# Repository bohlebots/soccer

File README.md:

# Bohlebots
<h2>collection of all published and open source software and hardware from the Bohlebots.</h2>
We are a team of students at the Gymnasium Haan in Germany. We call ourselves Bohlebots
due to the support of the Bohle company at our home town Haan.

We decided to put all our robotic stuff opensource. This includes arduino files and libraries,
eagle pcb files () and eagle libraries (lbr) for all our baords.
This page is under construction and it suffers from the inactivity of the author.
BUT:

We are also taking part at the development of the https://github.com/CoRoSoN-Kit/CoRoSoN-Kit.
The aktual bohlbots CoRoSoN Kit is lokated under https://github.com/ItzJannis/CoRoSoN-Package_Draft

Here is a photo of the prototypes of a mainboard and an IR-seeker-ring:

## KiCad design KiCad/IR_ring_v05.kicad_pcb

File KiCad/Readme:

These are the current KiCad project files of the season 2024.
These boards are used by the bohlebots 1vs1 teams and can be used as CoRoSoN Kit boards as well

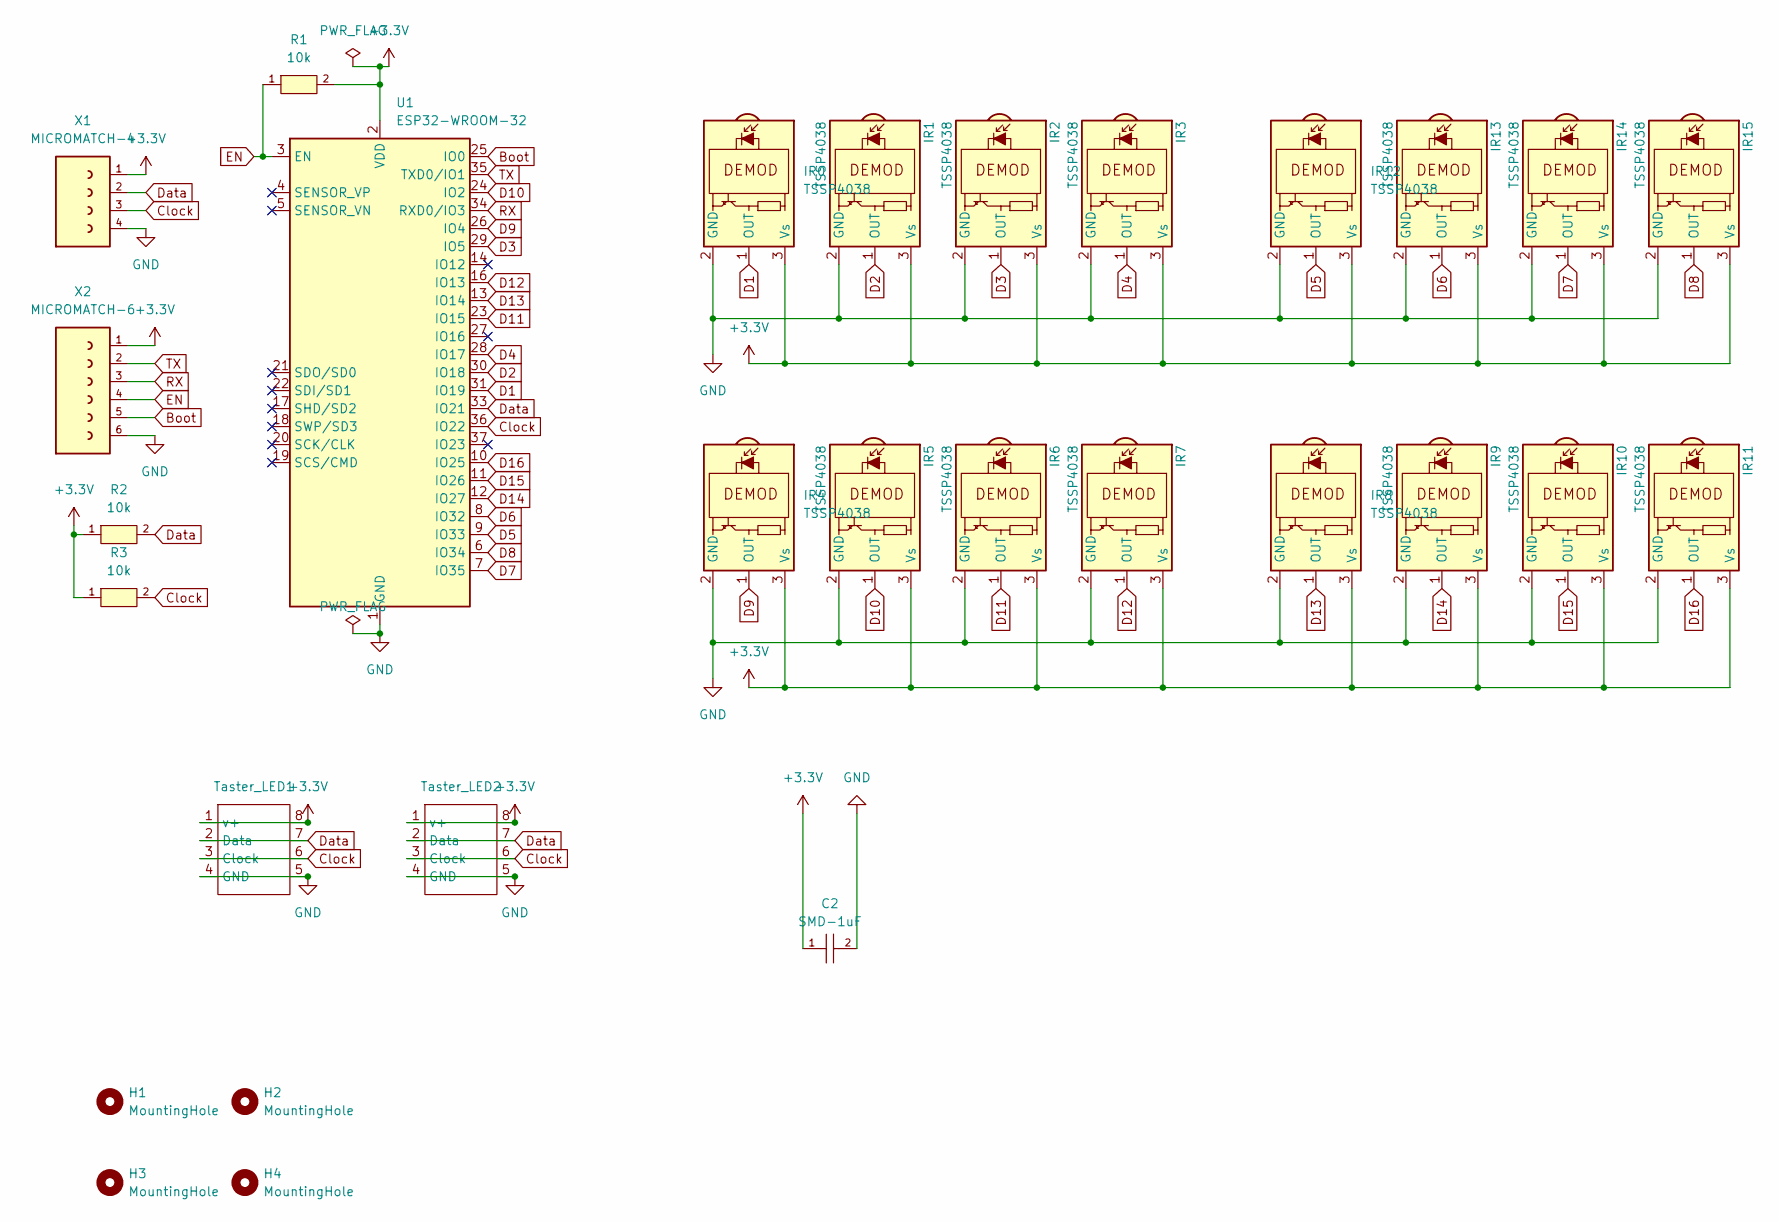
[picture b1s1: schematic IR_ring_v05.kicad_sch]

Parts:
C2: SMD-1uF; C0603; LCSC C1592
H1, H2, H3, H4: MountingHole; MountingHole_4.3mm_M4
IR0, IR1, IR2, IR3, IR4, IR5, IR6, IR7, IR8, IR9, IR10, IR11, IR12, IR13, IR14, IR15: TSSP4038; SENSOR-TH_TSSP40X_verschoben; LCSC Part # C143753
R1, R2, R3: 10k; R0603; LCSC C465463
Taster_LED1, Taster_LED2: TASTER_LED
U1: ESP32-WROOM-32; ESP32-WROOM-32-small; LCSC Part # C82899
X1: MICROMATCH-4
X2: MICROMATCH-6

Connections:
+3.3V: C2.1, IR0.3 (Vs), IR1.3 (Vs), IR2.3 (Vs), IR3.3 (Vs), IR4.3 (Vs), IR5.3 (Vs), IR6.3 (Vs), IR7.3 (Vs), IR8.3 (Vs), IR9.3 (Vs), IR10.3 (Vs), IR11.3 (Vs), IR12.3 (Vs), IR13.3 (Vs), IR14.3 (Vs), IR15.3 (Vs), R1.2, R2.1, R3.1, Taster_LED1.1 (v+), Taster_LED1.8, Taster_LED2.1 (v+), Taster_LED2.8, U1.2 (VDD), X1.1, X2.1
Boot: U1.25 (IO0), X2.5
Clock: R3.2, Taster_LED1.3 (Clock), Taster_LED1.6, Taster_LED2.3 (Clock), Taster_LED2.6, U1.36 (IO22), X1.3
D1: IR0.1 (OUT), U1.31 (IO19)
D2: IR1.1 (OUT), U1.30 (IO18)
D3: IR2.1 (OUT), U1.29 (IO5)
D4: IR3.1 (OUT), U1.28 (IO17)
D5: IR12.1 (OUT), U1.9 (IO33)
D6: IR13.1 (OUT), U1.8 (IO32)
D7: IR14.1 (OUT), U1.7 (IO35)
D8: IR15.1 (OUT), U1.6 (IO34)
D9: IR4.1 (OUT), U1.26 (IO4)
D10: IR5.1 (OUT), U1.24 (IO2)
D11: IR6.1 (OUT), U1.23 (IO15)
D12: IR7.1 (OUT), U1.16 (IO13)
D13: IR8.1 (OUT), U1.13 (IO14)
D14: IR9.1 (OUT), U1.12 (IO27)
D15: IR10.1 (OUT), U1.11 (IO26)
D16: IR11.1 (OUT), U1.10 (IO25)
Data: R2.2, Taster_LED1.2 (Data), Taster_LED1.7, Taster_LED2.2 (Data), Taster_LED2.7, U1.33 (IO21), X1.2
EN: R1.1, U1.3 (EN), X2.4
GND: C2.2, IR0.2 (GND), IR1.2 (GND), IR2.2 (GND), IR3.2 (GND), IR4.2 (GND), IR5.2 (GND), IR6.2 (GND), IR7.2 (GND), IR8.2 (GND), IR9.2 (GND), IR10.2 (GND), IR11.2 (GND), IR12.2 (GND), IR13.2 (GND), IR14.2 (GND), IR15.2 (GND), Taster_LED1.4 (GND), Taster_LED1.5, Taster_LED2.4 (GND), Taster_LED2.5, U1.1 (GND), U1.15 (GND), U1.38 (GND), U1.39 (GND), X1.4, X2.6
RX: U1.34 (RXD0/IO3), X2.3
TX: U1.35 (TXD0/IO1), X2.2

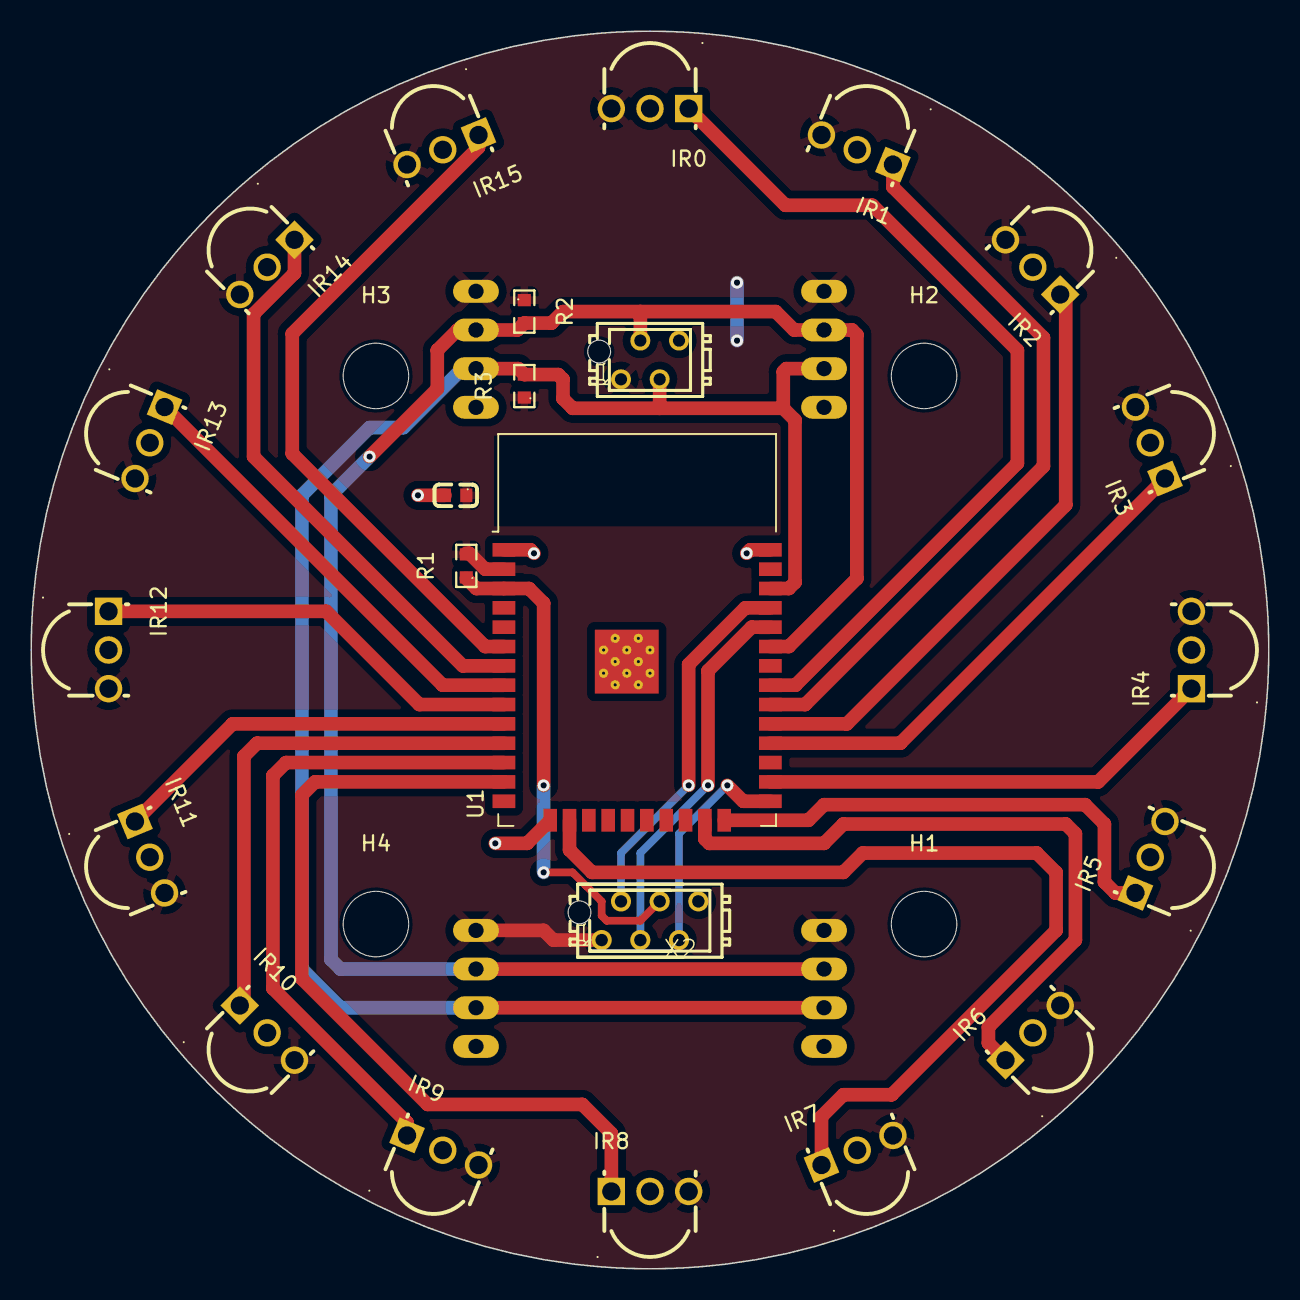
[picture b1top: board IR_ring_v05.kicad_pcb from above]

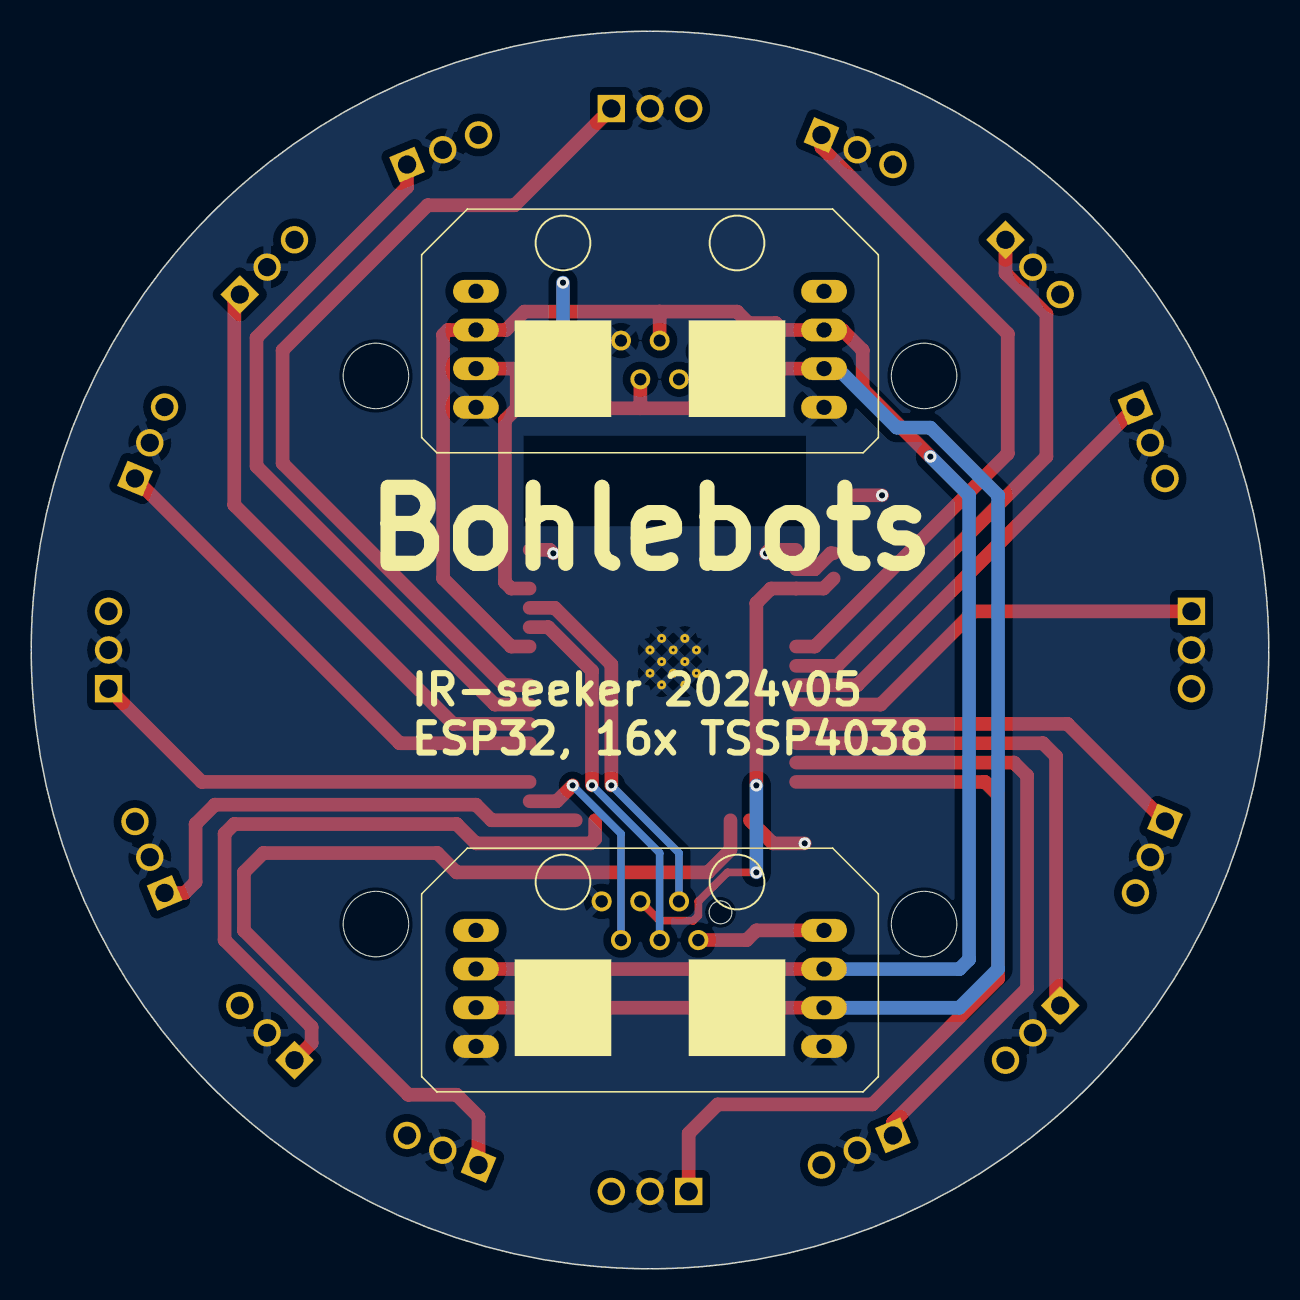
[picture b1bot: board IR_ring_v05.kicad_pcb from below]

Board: 2 copper layers, 81.3 x 81.3 mm, 29 parts (2 on the bottom side), 24 nets.

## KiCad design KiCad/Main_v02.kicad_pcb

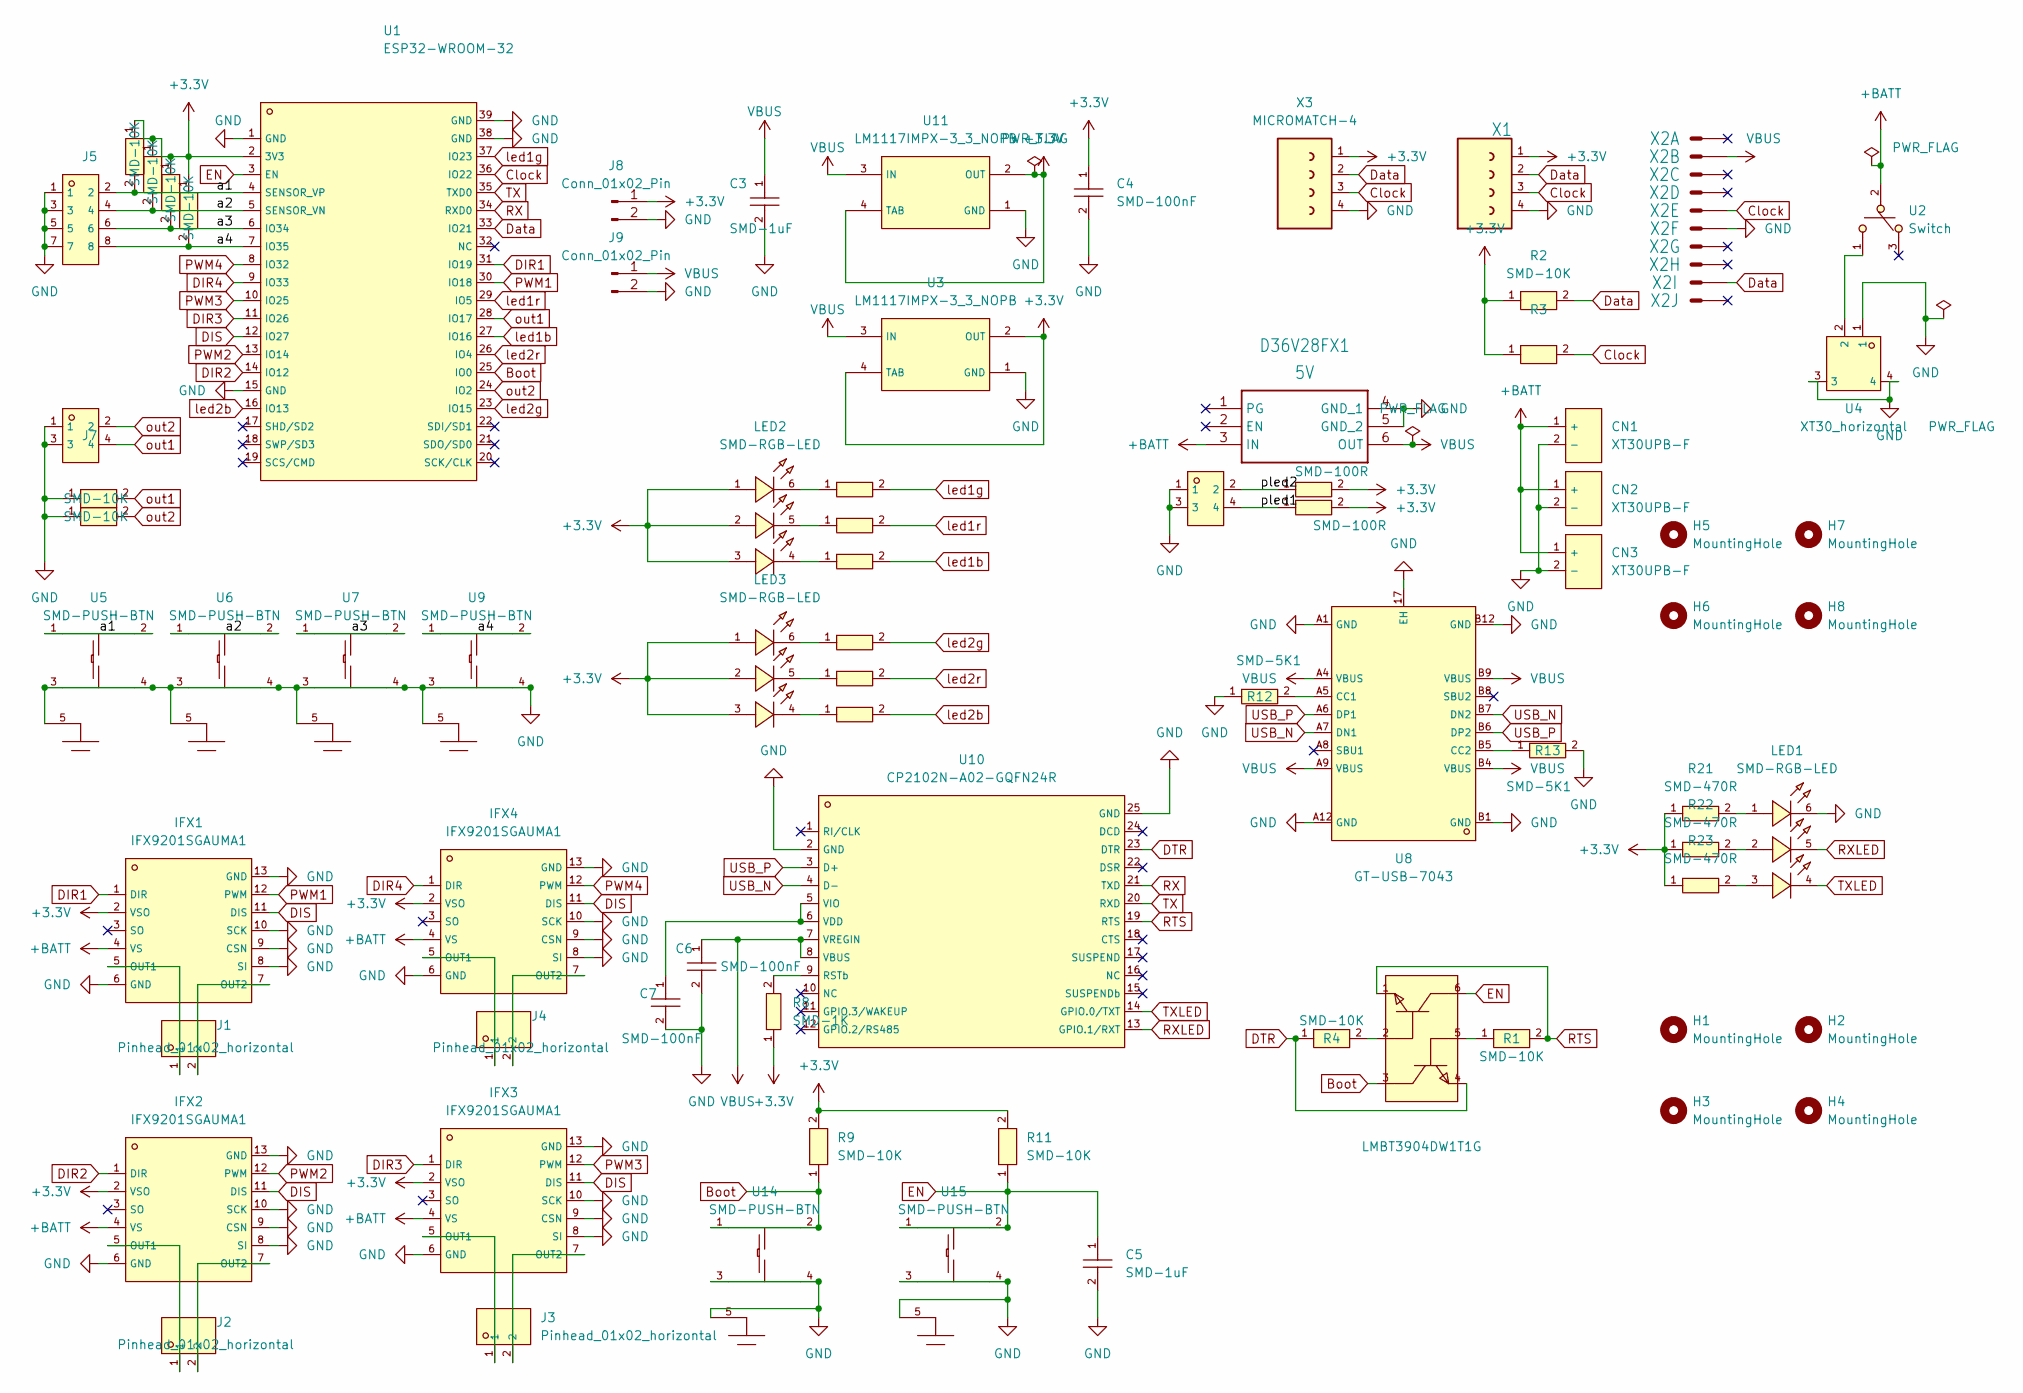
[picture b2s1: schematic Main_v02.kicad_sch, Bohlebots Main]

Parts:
C3, C5: SMD-1uF; C0603; LCSC C1592
C4, C6, C7: SMD-100nF; C0603; LCSC C30926
CN1, CN2, CN3: XT30UPB-F; CONN-TH_XT30UPB-F; LCSC C108769
D36V28FX1: 5V; D36V28FX
H1, H2, H3, H4, H5, H6, H7, H8: MountingHole; MountingHole_4.3mm_M4
IFX1, IFX2, IFX3, IFX4: IFX9201SGAUMA1; SO-12_L6.4-W7.5-P1.00-LS10.3-BL-EP; LCSC C112633
J1, J2, J3, J4: Pinhead_01x02_horizontal; HDR-TH_2P-P2.54-H-M-W10.4; LCSC C492410
J5: Conn_02x04_Row_Letter_First; HDR-TH_8P-P2.54-H-M-R2-C4-S2.54; LCSC C706885
J6, J7: Conn_02x02_Row_Letter_First; HDR-TH_4P-P2.54-H-M-R2-C2-S2.54-W12.3-N; LCSC C706883
J8, J9: Conn_01x02_Pin; PinHeader_1x02_P2.54mm_Vertical
LED1, LED2, LED3: SMD-RGB-LED; LED-SMD_6P-L5.0-W5.0-TL_TC5050RGBF08; LCSC C784540
R1, R2, R3, R4, R5, R6, R7, R9, R10, R11, R14, R15: SMD-10K; R0603; LCSC C465463
R8: SMD-1K; R0603; LCSC C22548
R12, R13: SMD-5K1; R0603; LCSC C103696
R16, R17, R20, R21, R22, R23, R24, R25, R26: SMD-470R; R0603; LCSC C23162
R18, R19: SMD-100R; R0603; LCSC C22775
U1: ESP32-WROOM-32; WIFIM-SMD_ESP32-WROOM-32-N4; LCSC C82899
U2: Switch; SW-TH_MT-0-103-A101-M200-RS; LCSC C1788498
U3, U11: LM1117IMPX-3_3_NOPB; SOT-223_L6.5-W3.5-P2.30-LS7.0-BR; LCSC C23984
U4: XT30_horizontal; CONN-TH_XT30PW-M; LCSC C431092
U5, U6, U7, U9, U14, U15: SMD-PUSH-BTN; SW-TH_5P-L6.0-W6.0-P4.50-LS6.5; LCSC C470256
U8: GT-USB-7043; USB-C-SMD_GT-USB-7043; LCSC C2762982
U10: CP2102N-A02-GQFN24R; QFN-24_L4.0-W4.0-P0.50-TL-EP2.6; LCSC C969151
U12: LMBT3904DW1T1G; SOT-363_L2.0-W1.3-P0.65-LS2.1-BR; LCSC C131781
X1: MICROMATCH-4
X2: MICROMATCH-10
X3: MICROMATCH-4

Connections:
+3.3V: C4.1, IFX1.2 (VSO), IFX2.2 (VSO), IFX3.2 (VSO), IFX4.2 (VSO), J8.1, LED2.1 (+), LED2.2 (+), LED2.3 (+), LED3.1 (+), LED3.2 (+), LED3.3 (+), R2.1, R3.1, R5.1, R6.1, R7.1, R8.1, R9.2, R10.1, R11.2, R18.2, R19.2, R21.1, R22.1, R23.1, U1.2 (3V3), U3.2 (OUT), U3.4 (TAB), U11.2 (OUT), U11.4 (TAB), X1.1, X3.1
+BATT: CN1.1 (+), CN2.1 (+), CN3.1 (+), D36V28FX1.3 (IN), IFX1.4 (VS), IFX2.4 (VS), IFX3.4 (VS), IFX4.4 (VS), U2.2
/a1: J5.2, R5.2, U1.4 (SENSOR_VP), U5.1, U5.2
/a2: J5.4, R6.2, U1.5 (SENSOR_VN), U6.1, U6.2
/a3: J5.6, R7.2, U1.6 (IO34), U7.1, U7.2
/a4: J5.8, R10.2, U1.7 (IO35), U9.1, U9.2
/pled1: J6.4, R19.1
/pled2: J6.2, R18.1
Boot: R9.1, U1.25 (IO0), U12.3 (C), U14.1, U14.2
Clock: R3.2, U1.36 (IO22), X1.3, X2.5 (S), X3.3
DIR1: IFX1.1 (DIR), U1.31 (IO19)
DIR2: IFX2.1 (DIR), U1.14 (IO12)
DIR3: IFX3.1 (DIR), U1.11 (IO26)
DIR4: IFX4.1 (DIR), U1.9 (IO33)
DIS: IFX1.11 (DIS), IFX2.11 (DIS), IFX3.11 (DIS), IFX4.11 (DIS), U1.12 (IO27)
DTR: R4.1, U10.23 (DTR), U12.4 (E)
Data: R2.2, U1.33 (IO21), X1.2, X2.9 (S), X3.2
EN: C5.1, R11.1, U1.3 (EN), U12.6 (C), U15.1, U15.2
GND: C3.2, C4.2, C5.2, C6.2, C7.2, CN1.2 (-), CN2.2 (-), CN3.2 (-), D36V28FX1.4 (GND_1), D36V28FX1.5 (GND_2), IFX1.6 (GND), IFX1.8 (SI), IFX1.9 (CSN), IFX1.10 (SCK), IFX1.13 (GND), IFX2.6 (GND), IFX2.8 (SI), IFX2.9 (CSN), IFX2.10 (SCK), IFX2.13 (GND), IFX3.6 (GND), IFX3.8 (SI), IFX3.9 (CSN), IFX3.10 (SCK), IFX3.13 (GND), IFX4.6 (GND), IFX4.8 (SI), IFX4.9 (CSN), IFX4.10 (SCK), IFX4.13 (GND), J5.1, J5.3, J5.5, J5.7, J6.1, J6.3, J7.1, J7.3, J8.2, J9.2, LED1.6 (-), R12.1, R13.2, R14.1, R15.1, U1.1 (GND), U1.15 (GND), U1.38 (GND), U1.39 (GND), U3.1 (GND), U4.1, U4.3, U4.4, U5.3, U5.4, U5.5, U6.3, U6.4, U6.5, U7.3, U7.4, U7.5, U8.17 (EH), U8.A1 (GND), U8.A12 (GND), U8.B1 (GND), U8.B12 (GND), U9.3, U9.4, U9.5, U10.2 (GND), U10.25 (GND), U11.1 (GND), U14.3, U14.4, U14.5, U15.3, U15.4, U15.5, X1.4, X2.6 (S), X3.4
unnamed: IFX1.5 (OUT1), J1.1
unnamed: IFX1.7 (OUT2), J1.2
unnamed: IFX2.5 (OUT1), J2.1
unnamed: IFX2.7 (OUT2), J2.2
unnamed: IFX3.5 (OUT1), J3.1
unnamed: IFX3.7 (OUT2), J3.2
unnamed: IFX4.5 (OUT1), J4.1
unnamed: IFX4.7 (OUT2), J4.2
unnamed: LED1.1 (+), R21.2
unnamed: LED1.2 (+), R22.2
unnamed: LED1.3 (+), R23.2
unnamed: LED2.4 (-), R20.1
unnamed: LED2.5 (-), R17.1
unnamed: LED2.6 (-), R16.1
unnamed: LED3.4 (-), R26.1
unnamed: LED3.5 (-), R25.1
unnamed: LED3.6 (-), R24.1
unnamed: R1.1, U12.5 (B)
unnamed: R4.2, U12.2 (B)
unnamed: U2.1, U4.2
unnamed: R12.2, U8.A5 (CC1)
unnamed: R13.1, U8.B5 (CC2)
unnamed: R8.2, U10.9 (RSTb)
unnamed: C7.1, U10.5 (VIO), U10.6 (VDD)
PWM1: IFX1.12 (PWM), U1.30 (IO18)
PWM2: IFX2.12 (PWM), U1.13 (IO14)
PWM3: IFX3.12 (PWM), U1.10 (IO25)
PWM4: IFX4.12 (PWM), U1.8 (IO32)
RTS: R1.2, U10.19 (RTS), U12.1 (E)
RX: U1.34 (RXD0), U10.21 (TXD)
RXLED: LED1.5 (-), U10.13 (GPIO.1/RXT)
TX: U1.35 (TXD0), U10.20 (RXD)
TXLED: LED1.4 (-), U10.14 (GPIO.0/TXT)
USB_N: U8.A7 (DN1), U8.B7 (DN2), U10.4 (D-)
USB_P: U8.A6 (DP1), U8.B6 (DP2), U10.3 (D+)
VBUS: C3.1, C6.1, D36V28FX1.6 (OUT), J9.1, U3.3 (IN), U8.A4 (VBUS), U8.A9 (VBUS), U8.B4 (VBUS), U8.B9 (VBUS), U10.7 (VREGIN), U10.8 (VBUS), U11.3 (IN), X2.2 (S)
led1b: R20.2, U1.27 (IO16)
led1g: R16.2, U1.37 (IO23)
led1r: R17.2, U1.29 (IO5)
led2b: R26.2, U1.16 (IO13)
led2g: R24.2, U1.23 (IO15)
led2r: R25.2, U1.26 (IO4)
out1: J7.4, R14.2, U1.28 (IO17)
out2: J7.2, R15.2, U1.24 (IO2)

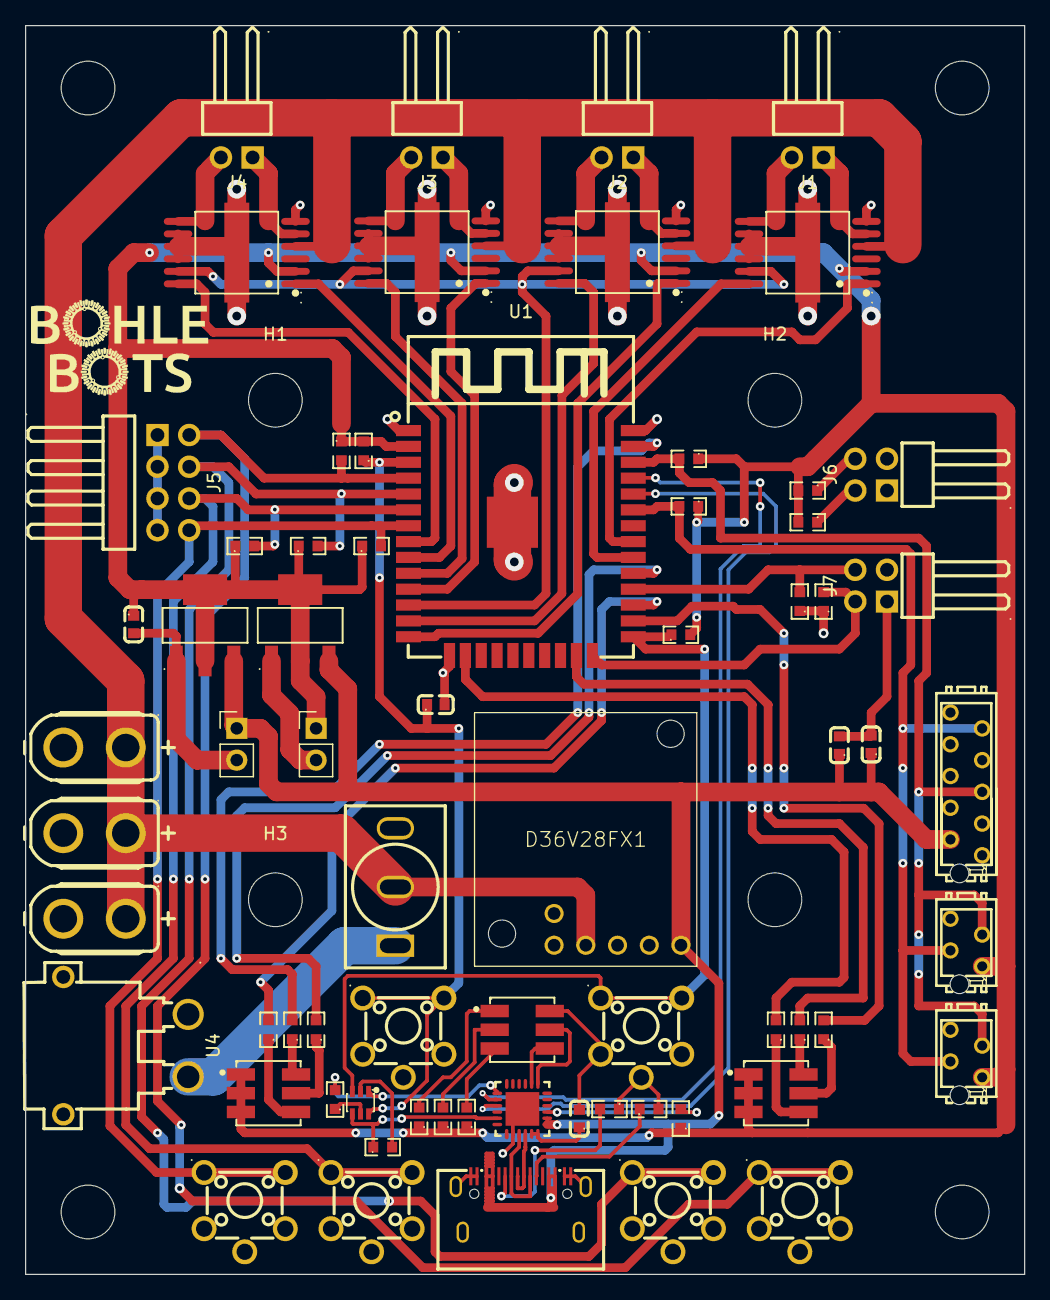
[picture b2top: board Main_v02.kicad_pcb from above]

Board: 2 copper layers, 80.0 x 100.0 mm, 76 parts (0 on the bottom side), 63 nets.

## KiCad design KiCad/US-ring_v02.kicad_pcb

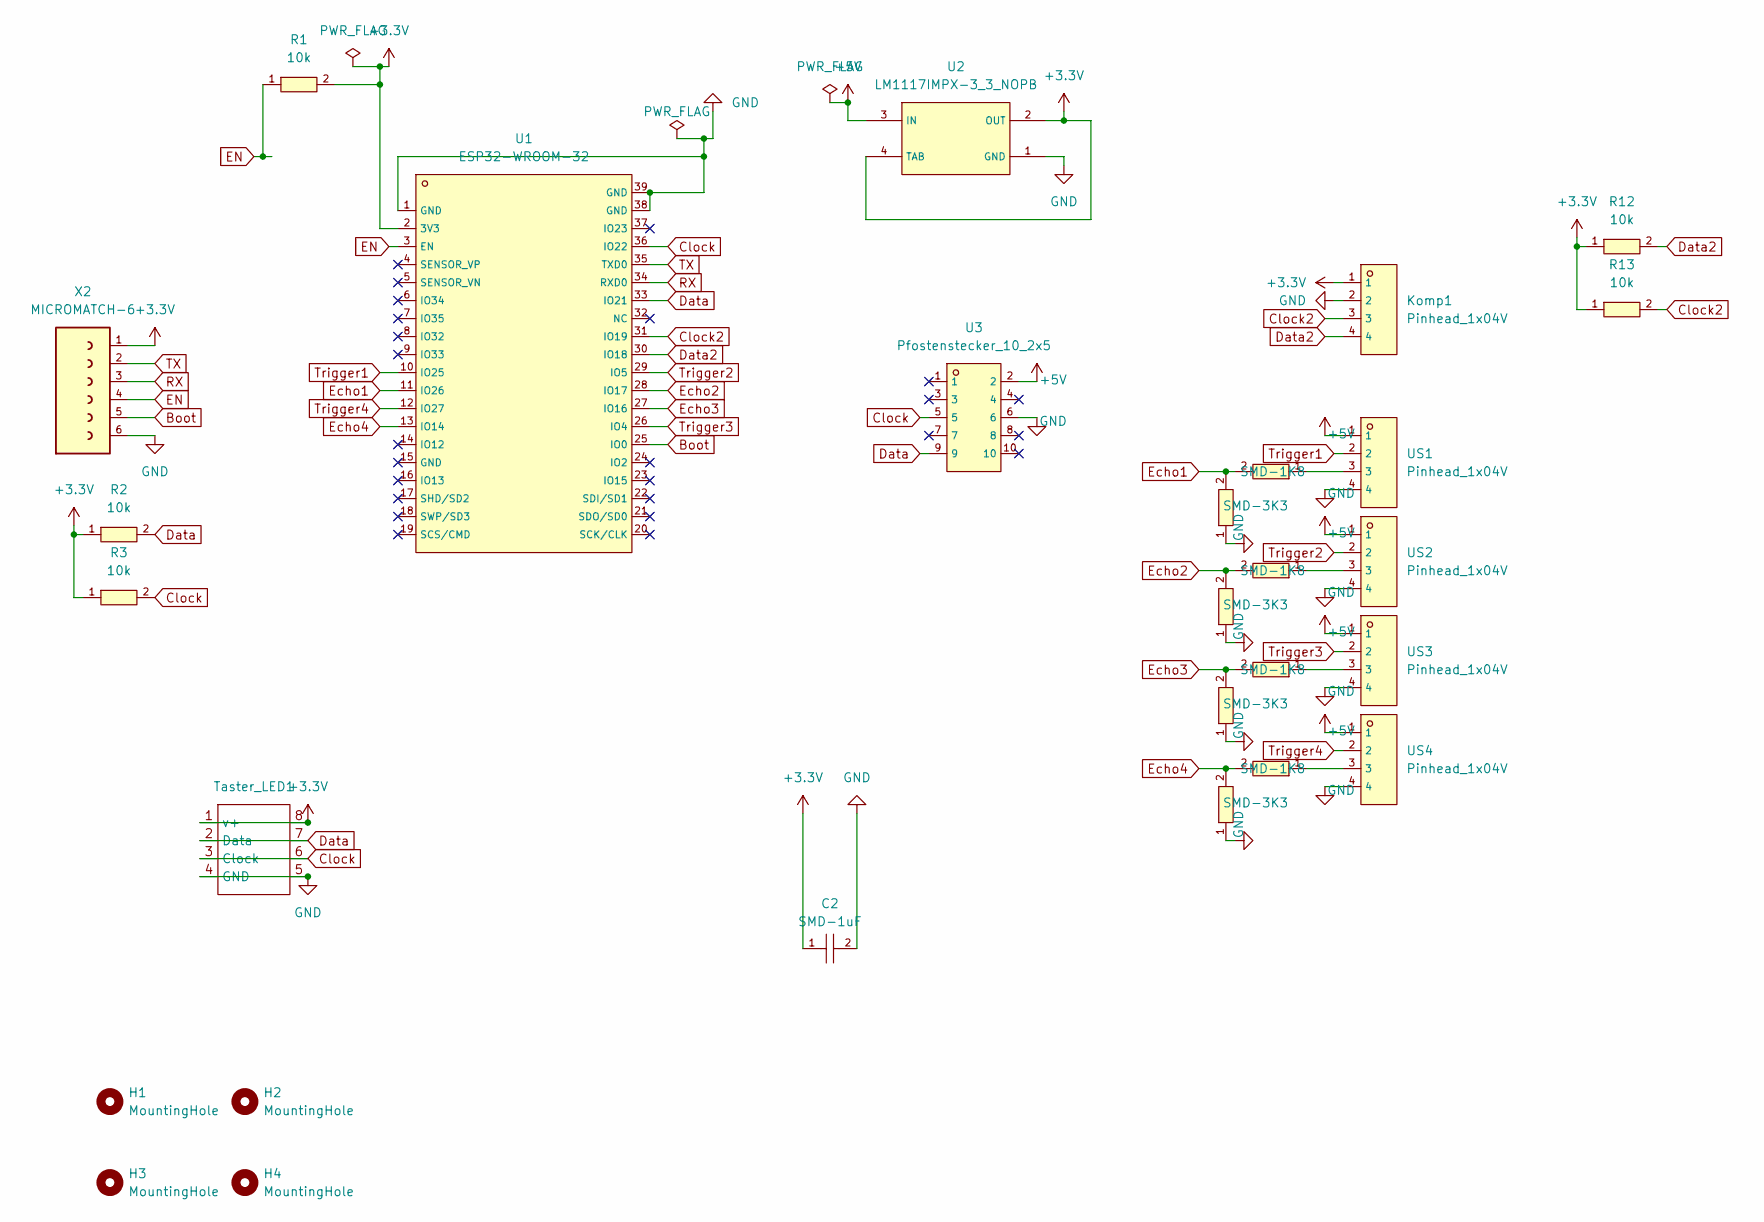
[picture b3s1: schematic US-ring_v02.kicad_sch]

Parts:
C2: SMD-1uF; C0603; LCSC C1592
H1, H2, H3, H4: MountingHole; MountingHole_4.3mm_M4
Komp1: Pinhead_1x04V; HDR-TH_4P-P2.54-V-M-1; LCSC C920779
R1, R2, R3, R12, R13: 10k; R0603; LCSC C25804
R4, R7, R8, R10: SMD-3K3; R0603; LCSC C22978
R5, R6, R9, R11: SMD-1K8; R0603; LCSC C4177
Taster_LED1: TASTER_LED
U1: ESP32-WROOM-32; WIFIM-SMD_ESP32-WROOM-32-N4; LCSC Part # C82899
U2: LM1117IMPX-3_3_NOPB; SOT-223_L6.5-W3.5-P2.30-LS7.0-BR; LCSC C23984
U3: Pfostenstecker_10_2x5; HDR-TH_10P-P2.54-V-F-R2-C5-S2.54-5; LCSC C5372865
US1, US2, US3, US4: Pinhead_1x04V; HDR-TH_4P-P2.54-V-M-1; LCSC C920779
X2: MICROMATCH-6

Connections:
+3.3V: C2.1, Komp1.1, R1.2, R2.1, R3.1, R12.1, R13.1, Taster_LED1.1 (v+), Taster_LED1.8, U1.2 (3V3), U2.2 (OUT), U2.4 (TAB), X2.1
+5V: U2.3 (IN), U3.2, US1.1, US2.1, US3.1, US4.1
Boot: U1.25 (IO0), X2.5
Clock: R3.2, Taster_LED1.3 (Clock), Taster_LED1.6, U1.36 (IO22), U3.5
Clock2: Komp1.3, R13.2, U1.31 (IO19)
Data: R2.2, Taster_LED1.2 (Data), Taster_LED1.7, U1.33 (IO21), U3.9
Data2: Komp1.4, R12.2, U1.30 (IO18)
EN: R1.1, U1.3 (EN), X2.4
Echo1: R10.2, R11.2, U1.11 (IO26)
Echo2: R6.2, R7.2, U1.28 (IO17)
Echo3: R4.2, R5.2, U1.27 (IO16)
Echo4: R8.2, R9.2, U1.13 (IO14)
GND: C2.2, Komp1.2, R4.1, R7.1, R8.1, R10.1, Taster_LED1.4 (GND), Taster_LED1.5, U1.1 (GND), U1.38 (GND), U1.39 (GND), U2.1 (GND), U3.6, US1.4, US2.4, US3.4, US4.4, X2.6
unnamed: R5.1, US3.3
unnamed: R6.1, US2.3
unnamed: R9.1, US4.3
unnamed: R11.1, US1.3
RX: U1.34 (RXD0), X2.3
TX: U1.35 (TXD0), X2.2
Trigger1: U1.10 (IO25), US1.2
Trigger2: U1.29 (IO5), US2.2
Trigger3: U1.26 (IO4), US3.2
Trigger4: U1.12 (IO27), US4.2

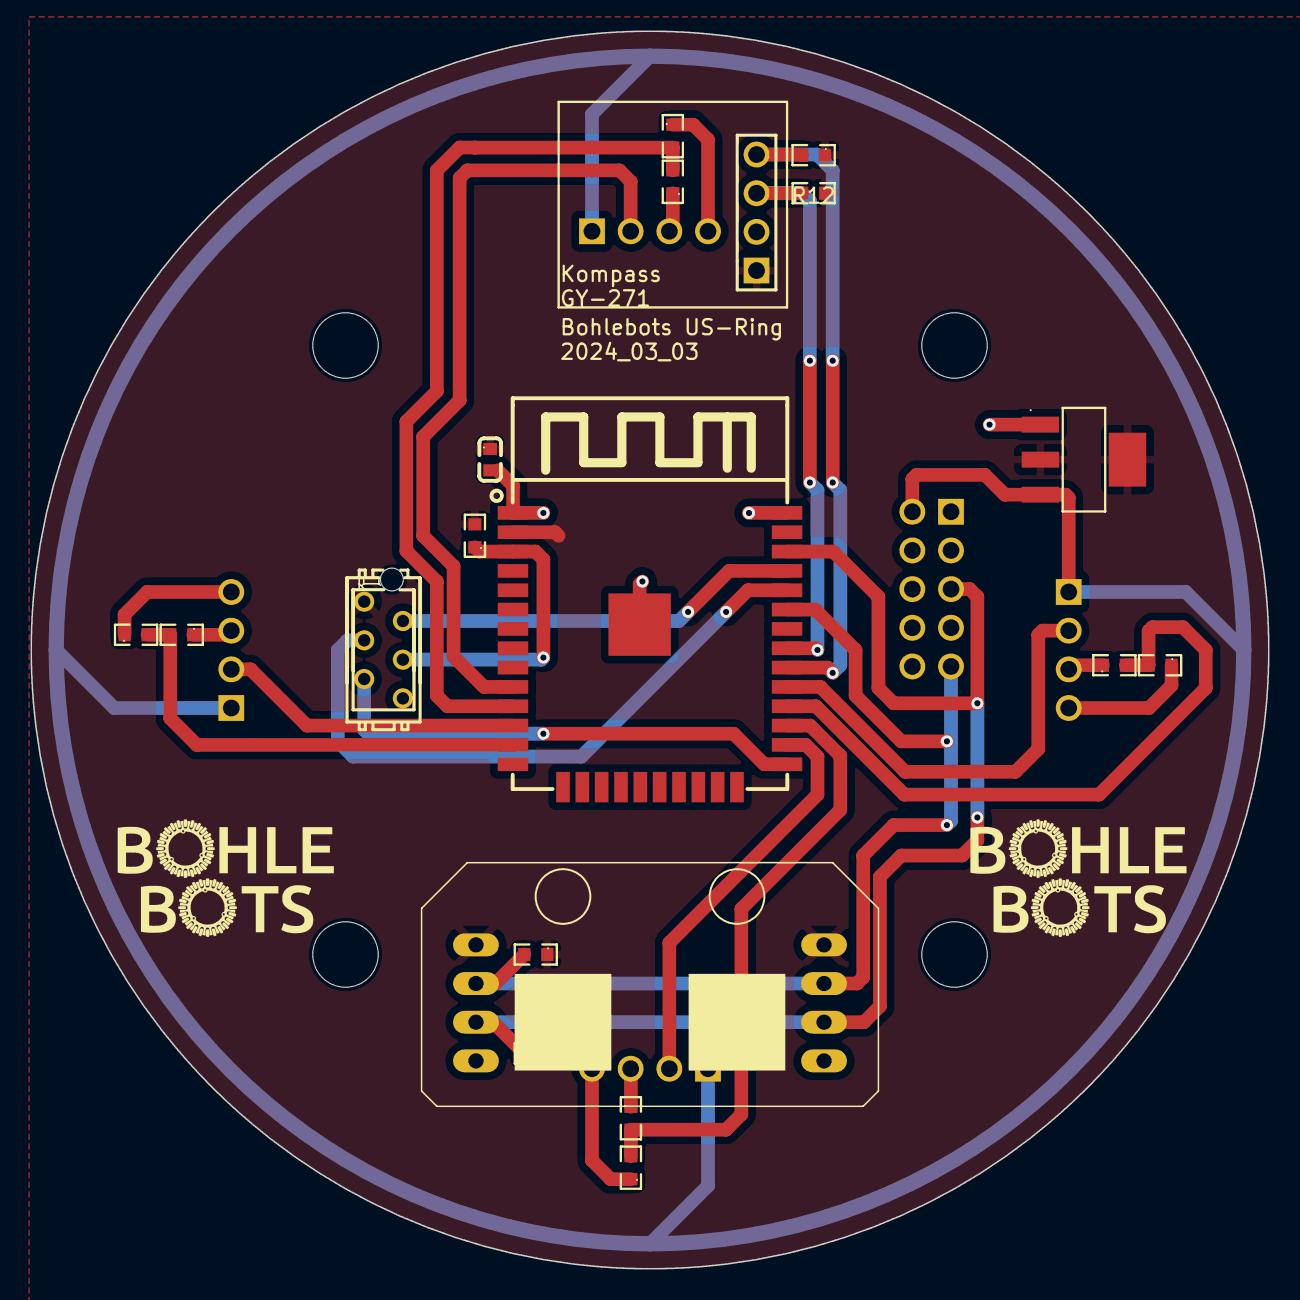
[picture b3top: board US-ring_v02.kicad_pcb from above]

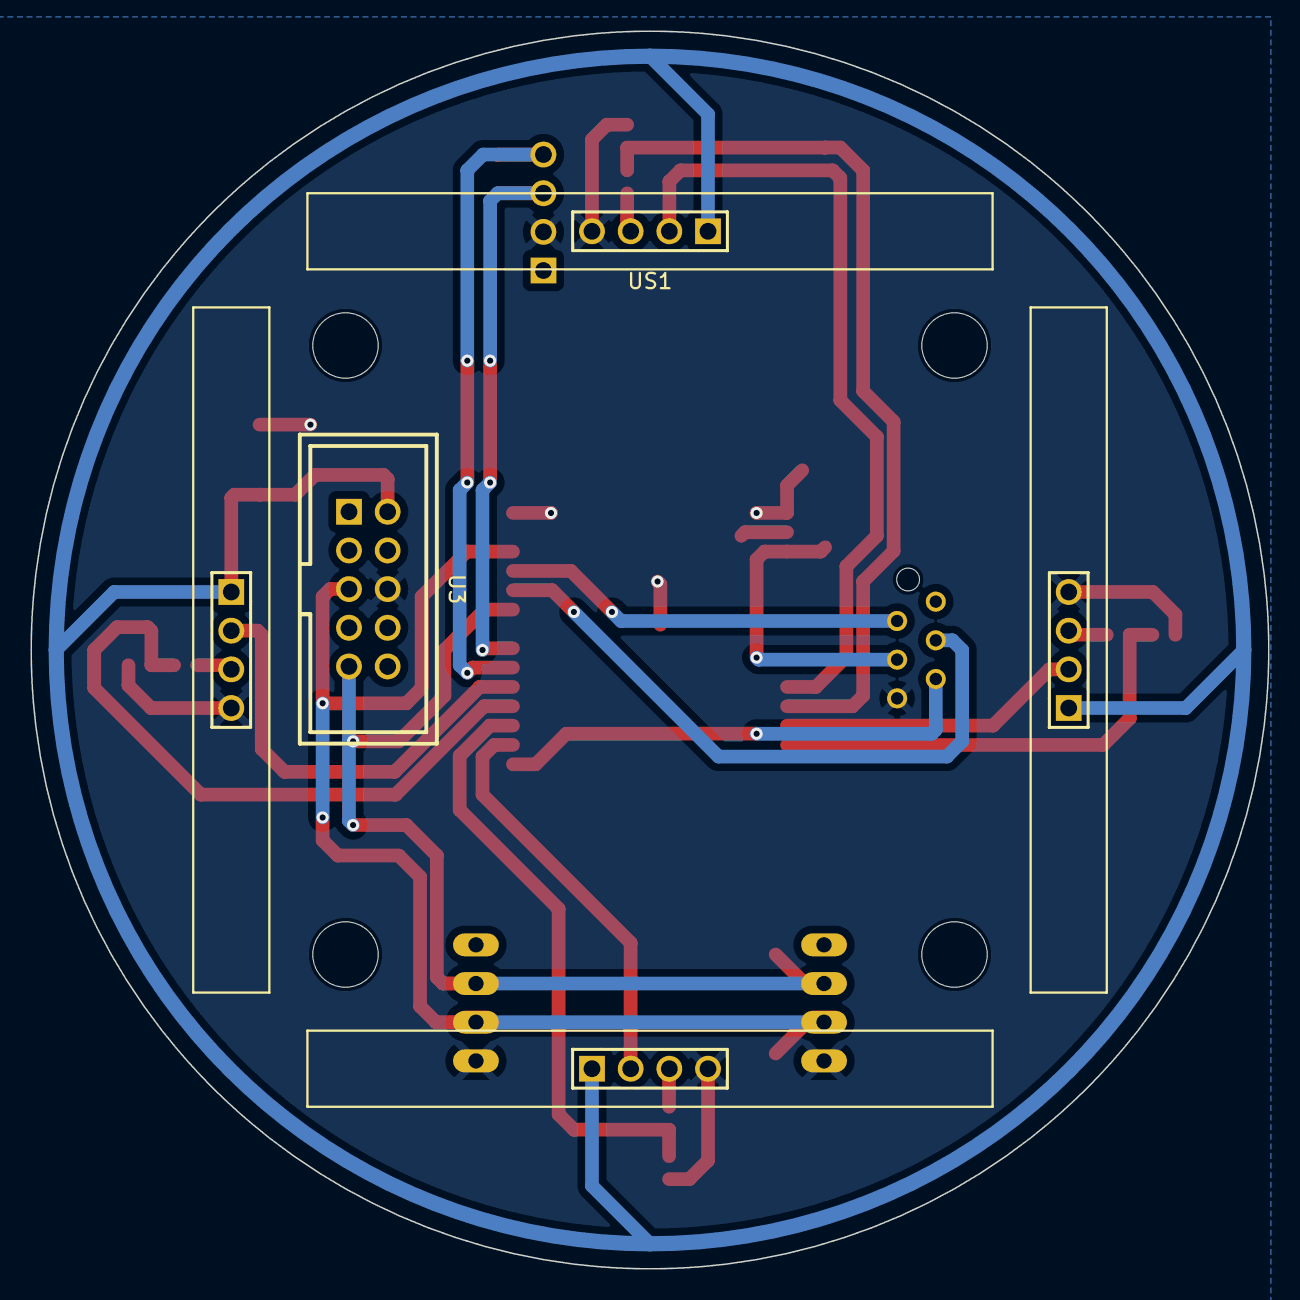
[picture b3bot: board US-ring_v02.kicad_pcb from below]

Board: 2 copper layers, 81.3 x 81.3 mm, 28 parts (5 on the bottom side), 23 nets.

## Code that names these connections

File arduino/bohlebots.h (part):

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#define MAGENTA 6
#define WEISS 7

#define led1r 5
#define led1g 23
#define led1b 16

#define led2r 4
#define led2g 15
#define led2b 13

/*
 * Festlegung der Motoren im bot-type-Betrieb
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    pinMode(kicker, OUTPUT);  digitalWrite(kicker, LOW);
    pinMode(dribbler, OUTPUT);digitalWrite(dribbler, LOW);

    pinMode(led1r, OUTPUT);
    digitalWrite(led1r, HIGH);
    pinMode(led1g, OUTPUT);
    digitalWrite(led1g, HIGH);
    pinMode(led1b, OUTPUT);
    digitalWrite(led1b, HIGH);
    pinMode(led2r, OUTPUT);
    digitalWrite(led2r, HIGH);
    pinMode(led2g, OUTPUT);
    digitalWrite(led2g, HIGH);
    pinMode(led2b, OUTPUT);
    digitalWrite(led2b, HIGH);

    Wire.begin(SDA, SCL);
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
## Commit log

2024-04-16 Create IR-Ring
